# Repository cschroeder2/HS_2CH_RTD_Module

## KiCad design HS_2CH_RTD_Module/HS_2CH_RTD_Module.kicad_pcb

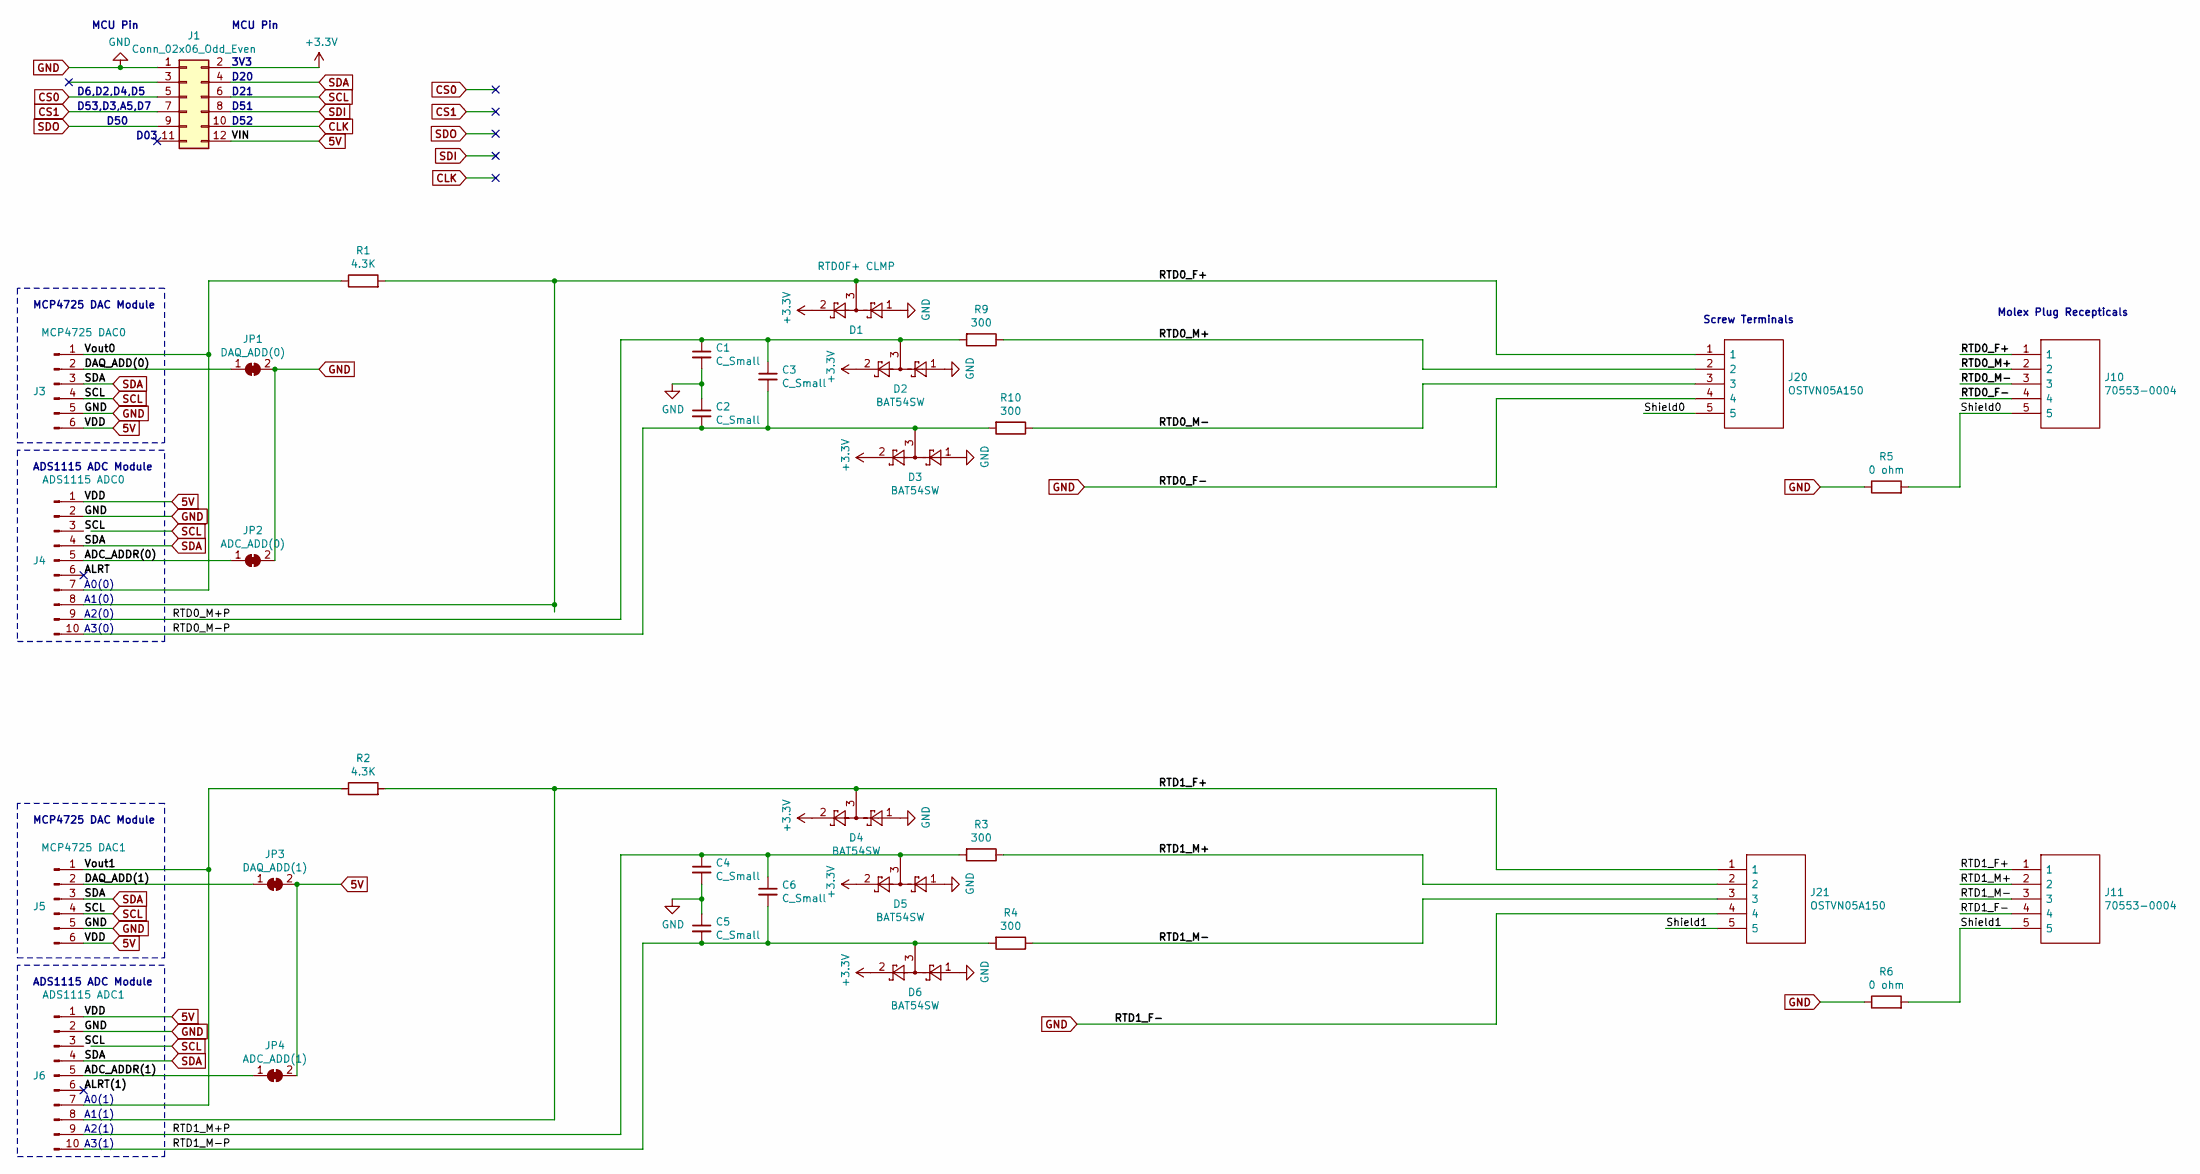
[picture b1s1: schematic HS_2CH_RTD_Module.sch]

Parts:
C1, C2, C3, C4, C5, C6: C_Small; C_0805_2012Metric_Pad1.15x1.40mm_HandSolder
D1: RTD0F+ CLMP; SOT-323_SC-70
D2, D3, D4, D5, D6: BAT54SW; SOT-323_SC-70
J1: Conn_02x06_Odd_Even
J3: MCP4725 DAC0; PinHeader_1x06_P2.54mm_Vertical
J4: ADS1115 ADC0; PinHeader_1x10_P2.54mm_Vertical
J5: MCP4725 DAC1; PinHeader_1x06_P2.54mm_Vertical
J6: ADS1115 ADC1; PinHeader_1x10_P2.54mm_Vertical
J10, J11: 70553-0004; PinHeader_1x05_P2.54mm_Vertical; Manufacturer_Part_Number 70553-0004; Mouser Part Number 538-70553-0004
J20, J21: OSTVN05A150; SHDR5W110P0X254_1X5_1310X650X850P; Manufacturer_Part_Number OSTVN05A150
JP1: DAQ_ADD(0); SolderJumper-2_P1.3mm_Bridged2Bar_RoundedPad1.0x1.5mm
JP2: ADC_ADD(0); SolderJumper-2_P1.3mm_Bridged2Bar_RoundedPad1.0x1.5mm
JP3: DAQ_ADD(1); SolderJumper-2_P1.3mm_Bridged2Bar_RoundedPad1.0x1.5mm
JP4: ADC_ADD(1); SolderJumper-2_P1.3mm_Bridged2Bar_RoundedPad1.0x1.5mm
R1, R2: 4.3K; R_0805_2012Metric_Pad1.15x1.40mm_HandSolder
R3, R4, R9, R10: 300; R_0805_2012Metric_Pad1.15x1.40mm_HandSolder
R5, R6: 0 ohm; R_0805_2012Metric_Pad1.15x1.40mm_HandSolder

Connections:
5V: J1.12, J3.6, J4.1, J5.6, J6.1, JP3.2 (B), JP4.2 (B)
+3V3: D1.2, D2.2, D3.2, D4.2, D5.2, D6.2, J1.2
/ADC_ADDR(0): J4.5, JP2.1 (A)
/ADC_ADDR(1): J6.5, JP4.1 (A)
/ALRT: J4.6
/ALRT(1): J6.6
/DAQ_ADD(0): J3.2, JP1.1 (A)
/DAQ_ADD(1): J5.2, JP3.1 (A)
/RTD0_F+: D1.3, J4.8, J10.1, J20.1, R1.2
/RTD0_M+: J10.2, J20.2, R9.1
/RTD0_M+P: C1.1, C3.1, D2.3, J4.9, R9.2
/RTD0_M-: J10.3, J20.3, R10.1
/RTD0_M-P: C2.2, C3.2, D3.3, J4.10, R10.2
/RTD1_F+: D4.3, J6.8, J11.1, J21.1, R2.2
/RTD1_M+: J11.2, J21.2, R3.1
/RTD1_M+P: C4.1, C6.1, D5.3, J6.9, R3.2
/RTD1_M-: J11.3, J21.3, R4.1
/RTD1_M-P: C5.2, C6.2, D6.3, J6.10, R4.2
/Shield0: J10.5, J20.5, R5.2
/Shield1: J11.5, J21.5, R6.2
/Vout0: J3.1, J4.7, R1.1
/Vout1: J5.1, J6.7, R2.1
CLK: J1.10
CS0: J1.5
CS1: J1.7
GND: C1.2, C2.1, C4.2, C5.1, D1.1, D2.1, D3.1, D4.1, D5.1, D6.1, J1.1, J3.5, J4.2, J5.5, J6.2, J10.4, J11.4, J20.4, J21.4, JP1.2 (B), JP2.2 (B), R5.1, R6.1
SCL: J1.6, J3.4, J4.3, J5.4, J6.3
SDA: J1.4, J3.3, J4.4, J5.3, J6.4
SDI: J1.8
SDO: J1.9

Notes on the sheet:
3V3
MCP4725 DAC Module
ADS1115 ADC Module
D20
D21
D51
D52
D03
D50
D53,D3,A5,D7
D6,D2,D4,D5
MCU Pin
Screw Terminals
Molex Plug Recepticals
A0(0)
A1(0)
A2(0)
A3(0)
A0(1)
A1(1)
A2(1)
A3(1)

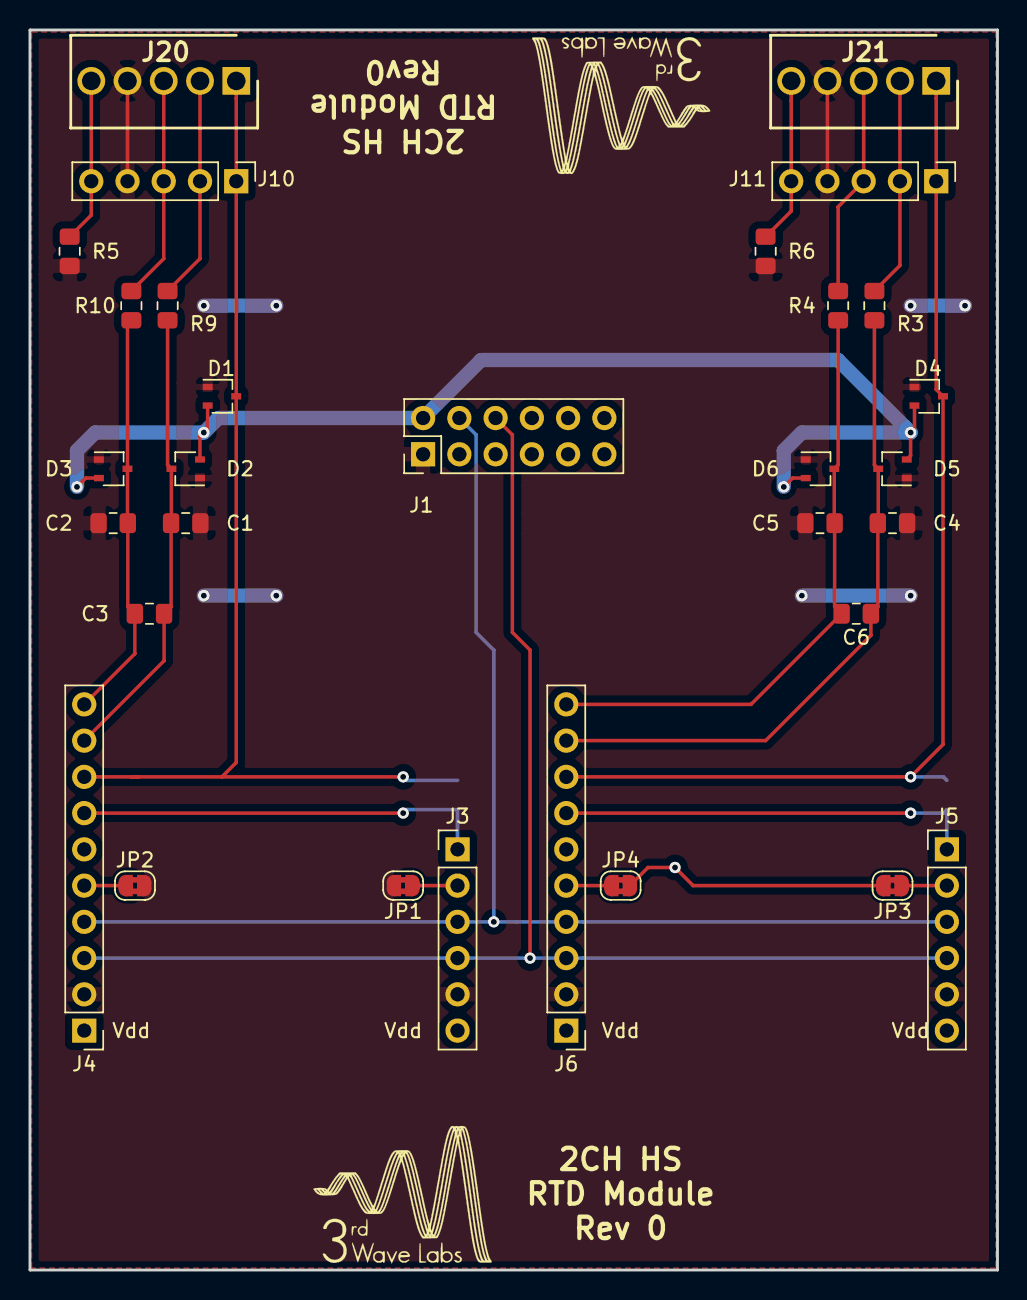
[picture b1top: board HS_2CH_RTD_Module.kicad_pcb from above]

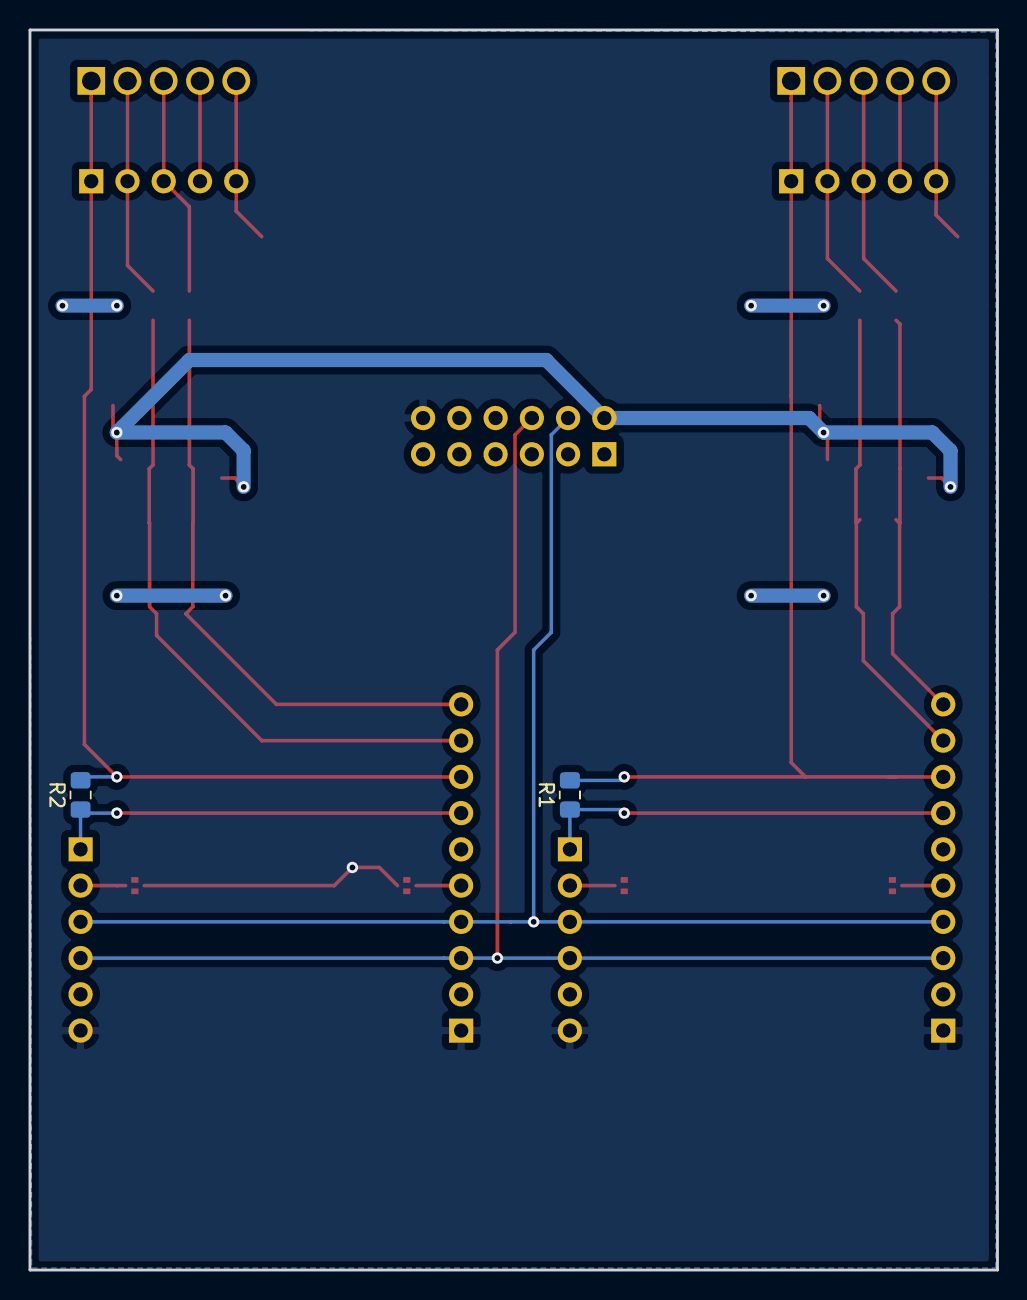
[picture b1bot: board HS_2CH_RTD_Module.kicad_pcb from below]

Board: 2 copper layers, 67.8 x 86.9 mm, 33 parts (2 on the bottom side), 23 nets.
